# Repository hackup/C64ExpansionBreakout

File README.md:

# C64ExpansionBreakout

This is an adapter board for the [expansion port](https://www.c64-wiki.com/wiki/Expansion_Port) of the Commodore 64. It connects the expansion port to a standard 830 pin prototyping breadboard to assist with the development of modules or cartridges. **USE AT YOUR OWN RISK!**

### Revision 2
This revision adds an optional on-board slot for either a 27c512 or 27c020 EPROM. The data bus lines D0-D7 and the address bus lines A0-A12 are connected directly to the slot, as are GND and the 5V power rail. The remaining address bus lines of the EPROM and CE/OE are available on J4. Jumper JP1 must be closed if a 27c512 chip is used.

### Revision 1
The first revision directly connects all 38 lines from the expansion port tho the breadboard. 5V and GND are connected to the matching rails on the breadboard. A reset button is added for convenience.

## License
[
](http://creativecommons.org/licenses/by-nc-sa/4.0/)

This work is licensed under a
[Creative Commons Attribution-NonCommercial-ShareAlike 4.0 International License](http://creativecommons.org/licenses/by-nc-sa/4.0/).

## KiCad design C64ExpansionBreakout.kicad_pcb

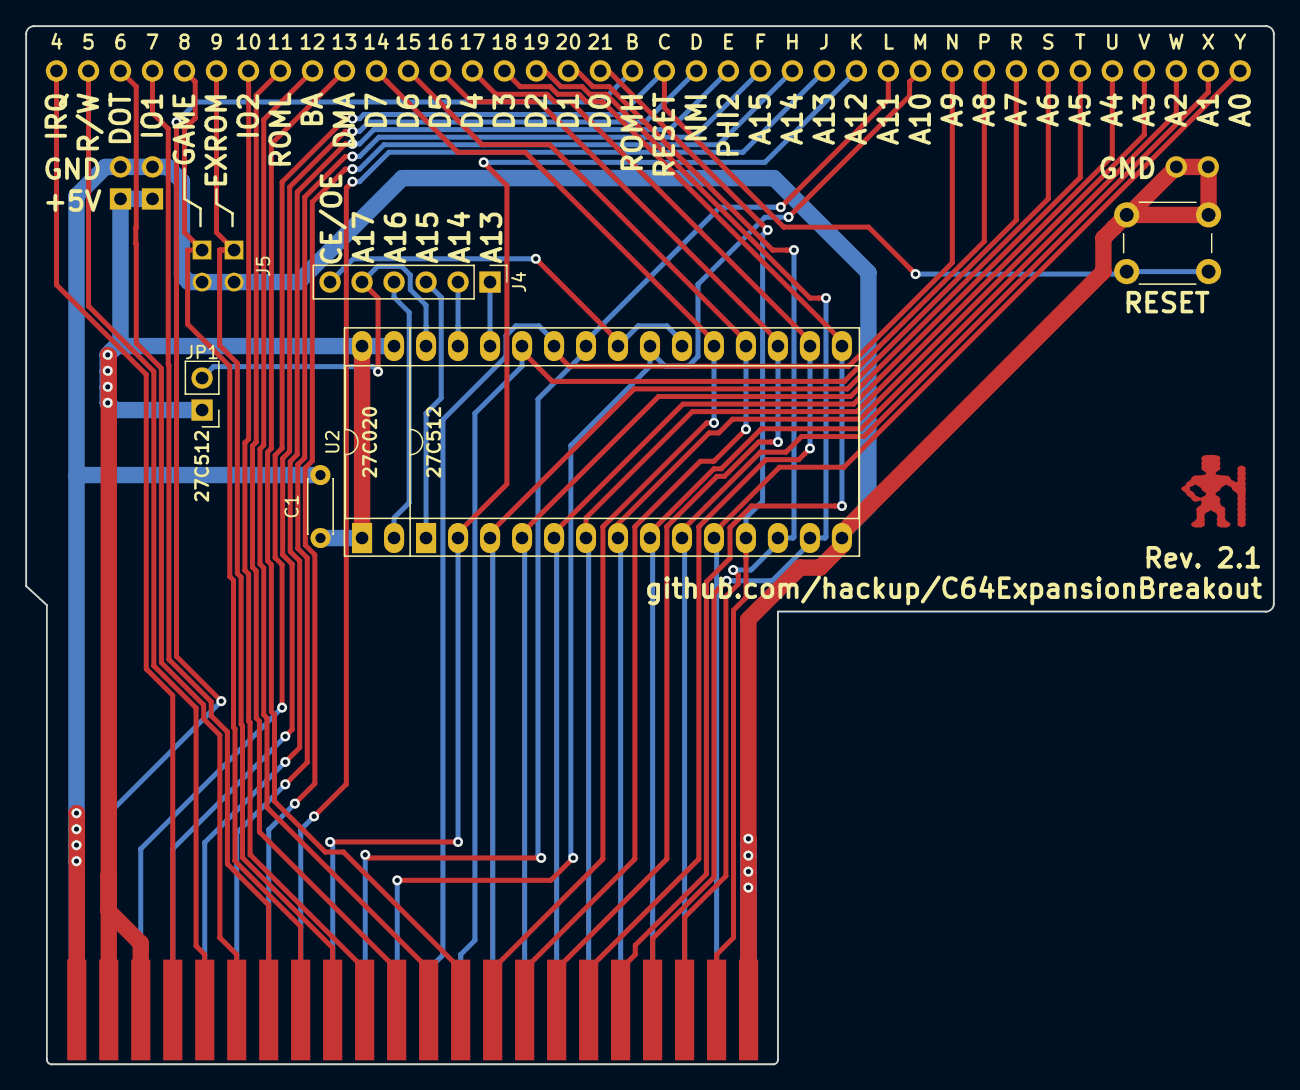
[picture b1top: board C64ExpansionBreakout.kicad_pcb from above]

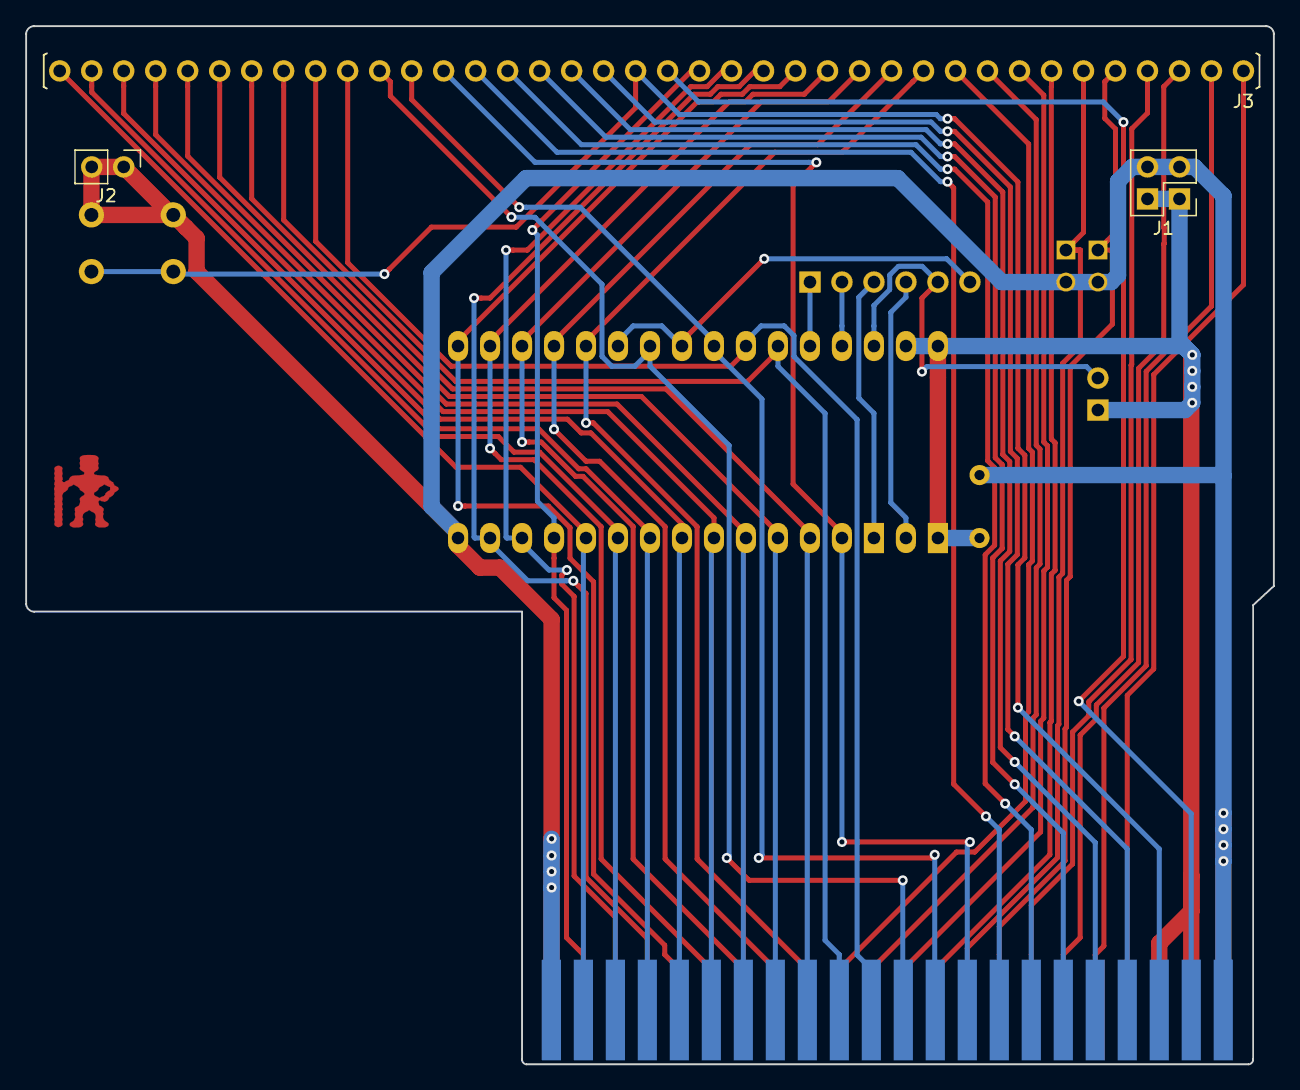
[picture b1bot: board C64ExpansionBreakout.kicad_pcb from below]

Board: 2 copper layers, 99.1 x 82.4 mm, 10 parts (3 on the bottom side), 46 nets.

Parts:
C1: 100n; C_Disc_D4.3mm_W1.9mm_P5.00mm
J1: Power; Pin_Header_Straight_2x02_Pitch2.54mm
J2: GND; Pin_Header_Straight_1x02_Pitch2.54mm
J3: Breakout; Pin_Header_Straight_1x38_Pitch2.54mm
J4: Other; Socket_Strip_Straight_1x06_Pitch2.54mm
J5: Config; Pin_Header_Straight_2x02_Pitch2.54mm
JP1: 27c512; Pin_Header_Straight_1x02_Pitch2.54mm
SW1: Reset; SW_PUSH_6mm
U1: C64-Exp-Port; C64-Cart-NoSilkS
U2: 27C512; DIP-32_W15.24mm_Socket_LongPads

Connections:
+5V: C1.1, J1.1, J1.2, JP1.1, U1.2, U1.3, U2.1, U2.31, U2.32
/CE: J4.6, U2.22, U2.24
/OA13: J4.1, U2.28
/OA14: J4.2, U2.29
/OA15: J4.3, U2.3
/OA16: J4.4, U2.2
/OA17: J4.5, JP1.2, U2.30
A0: J3.38, U1.Y, U2.12
A1: J3.37, U1.X, U2.11
A2: J3.36, U1.W, U2.10
A3: J3.35, U1.V, U2.9
A4: J3.34, U1.U, U2.8
A5: J3.33, U1.T, U2.7
A6: J3.32, U1.S, U2.6
A7: J3.31, U1.R, U2.5
A8: J3.30, U1.P, U2.27
A9: J3.29, U1.N, U2.26
A10: J3.28, U1.M, U2.23
A11: J3.27, U1.L, U2.25
A12: J3.26, U1.K, U2.4
A13: J3.25, U1.J
A14: J3.24, U1.H
A15: J3.23, U1.F
BA: J3.9, U1.12
D0: J3.18, U1.21, U2.13
D1: J3.17, U1.20, U2.14
D2: J3.16, U1.19, U2.15
D3: J3.15, U1.18, U2.17
D4: J3.14, U1.17, U2.18
D5: J3.13, U1.16, U2.19
D6: J3.12, U1.15, U2.20
D7: J3.11, U1.14, U2.21
DMA: J3.10, U1.13
DOT_CLK: J3.3, U1.6
EXROM: J3.6, J5.1, U1.9
GAME: J3.5, J5.3, U1.8
GND: C1.2, J1.3, J1.4, J2.1, J2.2, J5.2, J5.4, SW1.1, U1.1, U1.22, U1.A, U1.Z, U2.16
IO1: J3.4, U1.7
IO2: J3.7, U1.10
IRQ: J3.1, U1.4
NMI: J3.21, U1.D
PHI2: J3.22, U1.E
RESET: J3.20, SW1.2, U1.C
ROMH: J3.19, U1.B
ROML: J3.8, U1.11
RW: J3.2, U1.5

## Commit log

2018-04-10 Initial commit.
2018-04-10 Fine tuning.
2018-06-29 Copied/rescued connector symbols.
2018-09-03 Updated page settings.
2018-09-06 Added 27C512 / 27C020 Eprom socket.
2018-09-07 Finalizing revision 2.
2018-09-30 Drill holes not wide enough for ZIF socket.
2018-10-07 Revision update.
2018-10-07 Mark pins 1 again.
2018-10-07 Clean up libs.
2018-10-07 Added documentation.
2018-10-07 Added gerber files.
2018-10-30 Ready to order next batch.
2020-05-05 Updated readme with license information.
